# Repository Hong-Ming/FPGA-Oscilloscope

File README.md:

# FPGA Oscilloscope

## Table of Contents
- [Intorduction](#intorduction)
- [Directory Tree](#directory-tree)
- [Project Info](#project-info)
- [Framework and Layout](#framework-and-layout)
- [Contributor](#contributor)

## Intorduction
We built a simple oscilloscope using Nexys 4 DDR board and PCB. First, the PCB transforms the input voltage signal into a signal with an acceptable voltage range for the FPGA board input, as well as generating knobs' control signal. The FPGA board then takes the processed signal and control signal to display waveforms, change voltage scale, adjust sweep time, etc. This work is the final project of the Digital Laboratory class at NCTU. [ [Demo Video](https://www.youtube.com/watch?v=sgIzcKYEROs&feature=youtu.be&ab_channel=AlexLi) ]

## Directory Tree
<pre>
FPGA_Oscilloscope/
├─ Demo Video/ ..................... 
│  └─ Demo Video.mp4 ............... 
├─ FPGA_Code/ ...................... System Verilog code for oscilloscope
│  ├─ Oscilloscope.sv .............. Main Function
│  ├─ Control.sv ................... Function for processing control signal
│  ├─ Sampling.sv .................. Function for sampling signal
│  ├─ Data_transfer.sv ............. Choose sample data based on scale
│  ├─ Sampling_time.sv ............. Choose sample time based on scale
│  ├─ VGA.sv ....................... Function for displaying information on screen.
│  ├─ Trig_display.sv .............. Display trigger info
│  ├─ Time_display.sv .............. Display time info
│  ├─ Channel_display.sv ........... Display waveform
│  ├─ Info_display.sv .............. Subfunction for displaying info
│  ├─ Trig_info.sv ................. Subfunction for displaying info
│  ├─ Time_info.sv ................. Subfunction for displaying info
│  ├─ Scale_tag.sv ................. For output scale
│  ├─ Word.sv ...................... For bitmap-fonts
│  ├─ Word_move.sv ................. For bitmap-fonts
│  ├─ DFF.sv ....................... D Flip flop
│  ├─ clk_div_2.sv ................. Clock
│  ├─ Clk_div_4.sv ................. Clock
│  ├─ clk_div_16.sv ................ Clock
│  └─ clk_div_256.sv ............... Clock
└─ PCB/ ............................ Input rectifier circuit design
   ├─ MAX6818.lbr .................. ICL7660CAS Library File
   ├─ Oscilloscope.brd ............. PCB board file
   ├─ Oscilloscope.sch ............. PCB schematic file
   └─ Gerber/ ...................... Directory contains layout files
</pre>

## Project Info
- **HDL**: [SystemVerilog](https://en.wikipedia.org/wiki/SystemVerilog)
- **FPGA Board**: [Nexys 4 DDR](https://reference.digilentinc.com/reference/programmable-logic/nexys-4-ddr/start)
- **PCB Layout Software**: [EAGLE](https://www.autodesk.com/products/eagle/overview?plc=F360&term=1-YEAR&support=ADVANCED&quantity=1)

## Framework and Layout

**Framework**:

**Input Rectifier Circuit Schematic**:

**Input Rectifier Circuit Layout**:

## Contributor
- [Hong-Ming Chiu](https://hong-ming.github.io/)
- [Huan-Jung Lee]()

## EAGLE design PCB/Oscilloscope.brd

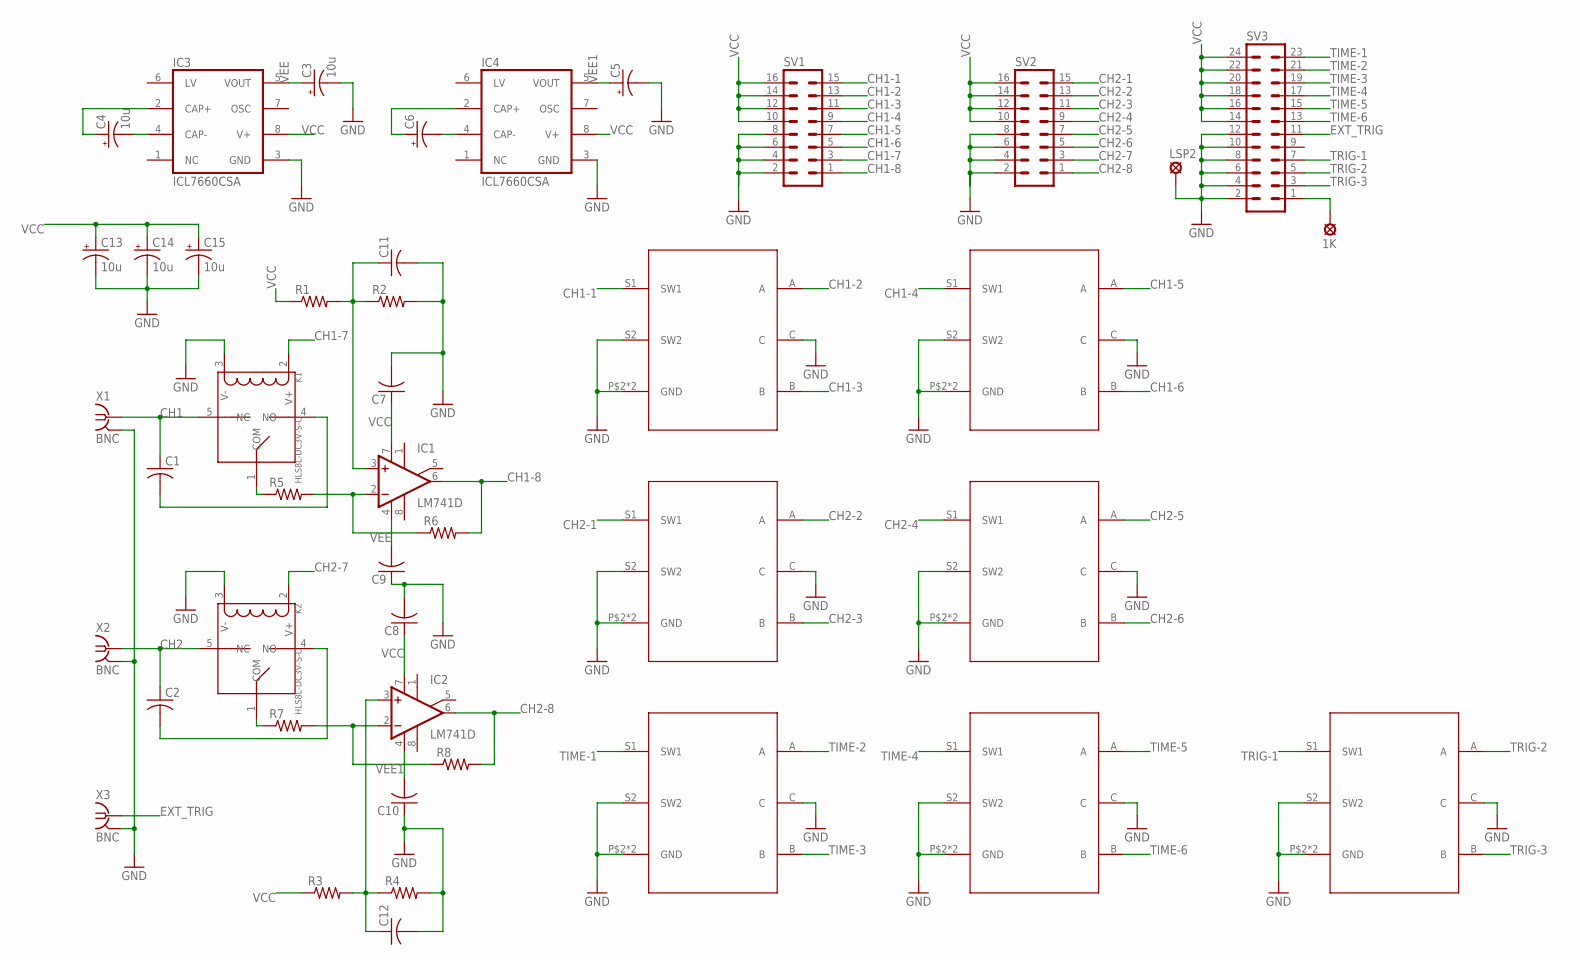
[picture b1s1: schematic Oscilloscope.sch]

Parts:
1K: LSP11
C1, C12: C-USC0402K; C0402K
C2, C7, C8, C9, C10, C11: C-USC0402; C0402
C3, C4, C13, C14, C15: 10u; E2-5
C5, C6: CPOL-USE2-5; E2-5
IC1, IC2: LM741D; SO08
IC3, IC4: ICL7660CSA; SO08
K1, K2: HLS8L-DC3V-S-C; REY5-19.0X15.0X15.0MM
LSP2: LSP11
R1, R2, R3, R4, R5, R6, R7, R8: R-US_R0402; R0402
SV1, SV2: MA08-2
SV3: MA12-2
U$2, U$3, U$4, U$5, U$6, U$7, U$8: EC11S
X1, X2, X3: BNC

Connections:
CH1: C1.1, K1.5 (NC), X1.P$1 (SIG)
CH1-1: SV1.15, U$3.S1 (SW1)
CH1-2: SV1.13, U$3.A
CH1-3: SV1.11, U$3.B
CH1-4: SV1.9, U$4.S1 (SW1)
CH1-5: SV1.7, U$4.A
CH1-6: SV1.5, U$4.B
CH1-7: K1.2 (V+), SV1.3
CH1-8: IC1.6 (OUT), R6.2, SV1.1
CH2: C2.1, K2.5 (NC), X2.P$1 (SIG)
CH2-1: SV2.15, U$2.S1 (SW1)
CH2-2: SV2.13, U$2.A
CH2-3: SV2.11, U$2.B
CH2-4: SV2.9, U$5.S1 (SW1)
CH2-5: SV2.7, U$5.A
CH2-6: SV2.5, U$5.B
CH2-7: K2.2 (V+), SV2.3
CH2-8: IC2.6 (OUT), R8.2, SV2.1
EXT_TRIG: SV3.11, X3.P$1 (SIG)
GND: C3.-, C5.-, C7.2, C8.2, C9.1, C10.1, C11.2, C12.2, C13.-, C14.-, C15.-, IC3.3 (GND), IC4.3 (GND), K1.3 (V-), K2.3 (V-), LSP2.MP, R2.2, R4.2, SV1.2, SV1.4, SV1.6, SV1.8, SV2.2, SV2.4, SV2.6, SV2.8, SV3.2, SV3.4, SV3.6, SV3.8, SV3.10, SV3.12, U$2.C, U$2.P$2 (GND), U$2.P$3 (GND), U$2.S2 (SW2), U$3.C, U$3.P$2 (GND), U$3.P$3 (GND), U$3.S2 (SW2), U$4.C, U$4.P$2 (GND), U$4.P$3 (GND), U$4.S2 (SW2), U$5.C, U$5.P$2 (GND), U$5.P$3 (GND), U$5.S2 (SW2), U$6.C, U$6.P$2 (GND), U$6.P$3 (GND), U$6.S2 (SW2), U$7.C, U$7.P$2 (GND), U$7.P$3 (GND), U$7.S2 (SW2), U$8.C, U$8.P$2 (GND), U$8.P$3 (GND), U$8.S2 (SW2), X1.P$2 (GND), X1.P$3 (GND), X1.P$4 (GND), X1.P$5 (GND), X2.P$2 (GND), X2.P$3 (GND), X2.P$4 (GND), X2.P$5 (GND), X3.P$2 (GND), X3.P$3 (GND), X3.P$4 (GND), X3.P$5 (GND)
unnamed: C1.2, K1.4 (NO)
unnamed: C2.2, K2.4 (NO)
unnamed: IC2.2 (-IN), R7.2, R8.1
unnamed: C4.-, IC3.4 (CAP-)
unnamed: C4.+, IC3.2 (CAP+)
unnamed: C6.-, IC4.4 (CAP-)
unnamed: C6.+, IC4.2 (CAP+)
unnamed: C11.1, IC1.3 (+IN), R1.2, R2.1
unnamed: C12.1, IC2.3 (+IN), R3.2, R4.1
unnamed: 1K.MP, SV3.1
unnamed: K1.1 (COM), R5.1
unnamed: IC1.2 (-IN), R5.2, R6.1
unnamed: K2.1 (COM), R7.1
TIME-1: SV3.23, U$6.S1 (SW1)
TIME-2: SV3.21, U$6.A
TIME-3: SV3.19, U$6.B
TIME-4: SV3.17, U$7.S1 (SW1)
TIME-5: SV3.15, U$7.A
TIME-6: SV3.13, U$7.B
TRIG-1: SV3.7, U$8.S1 (SW1)
TRIG-2: SV3.5, U$8.A
TRIG-3: SV3.3, U$8.B
VCC: C7.1, C8.1, C13.+, C14.+, C15.+, IC1.7 (V+), IC2.7 (V+), IC3.8 (V+), IC4.8 (V+), R1.1, R3.1, SV1.10, SV1.12, SV1.14, SV1.16, SV2.10, SV2.12, SV2.14, SV2.16, SV3.14, SV3.16, SV3.18, SV3.20, SV3.22, SV3.24
VEE: C3.+, C9.2, IC1.4 (V-), IC3.5 (VOUT)
VEE1: C5.+, C10.2, IC2.4 (V-), IC4.5 (VOUT)

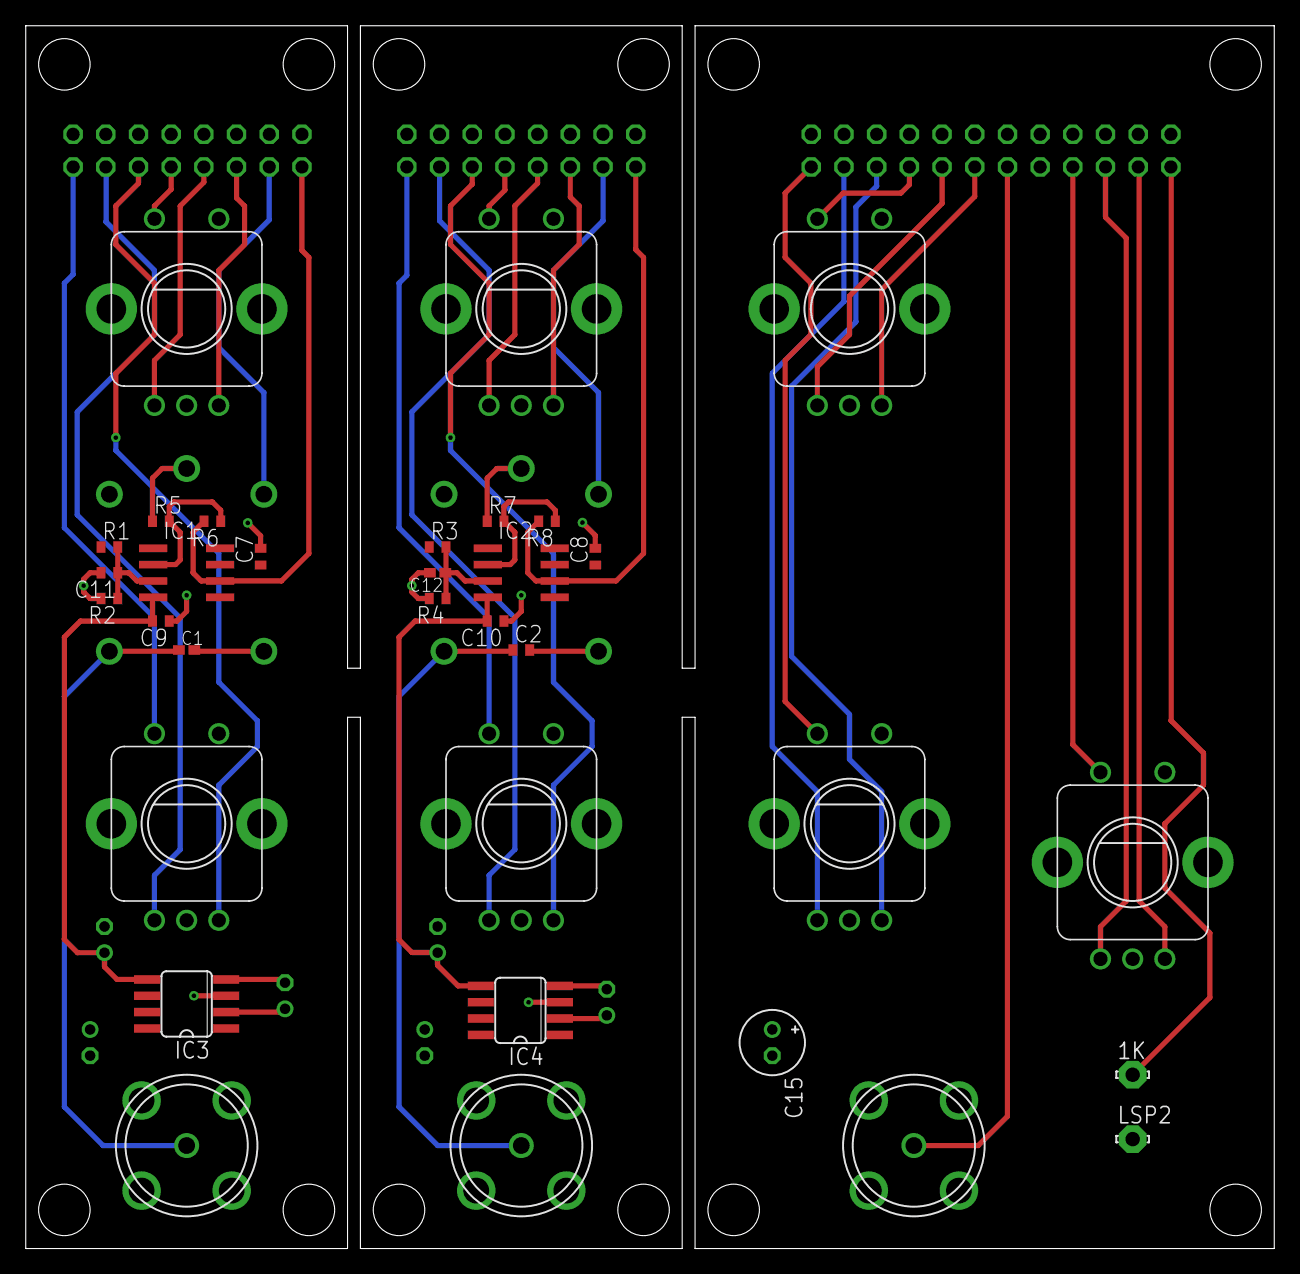
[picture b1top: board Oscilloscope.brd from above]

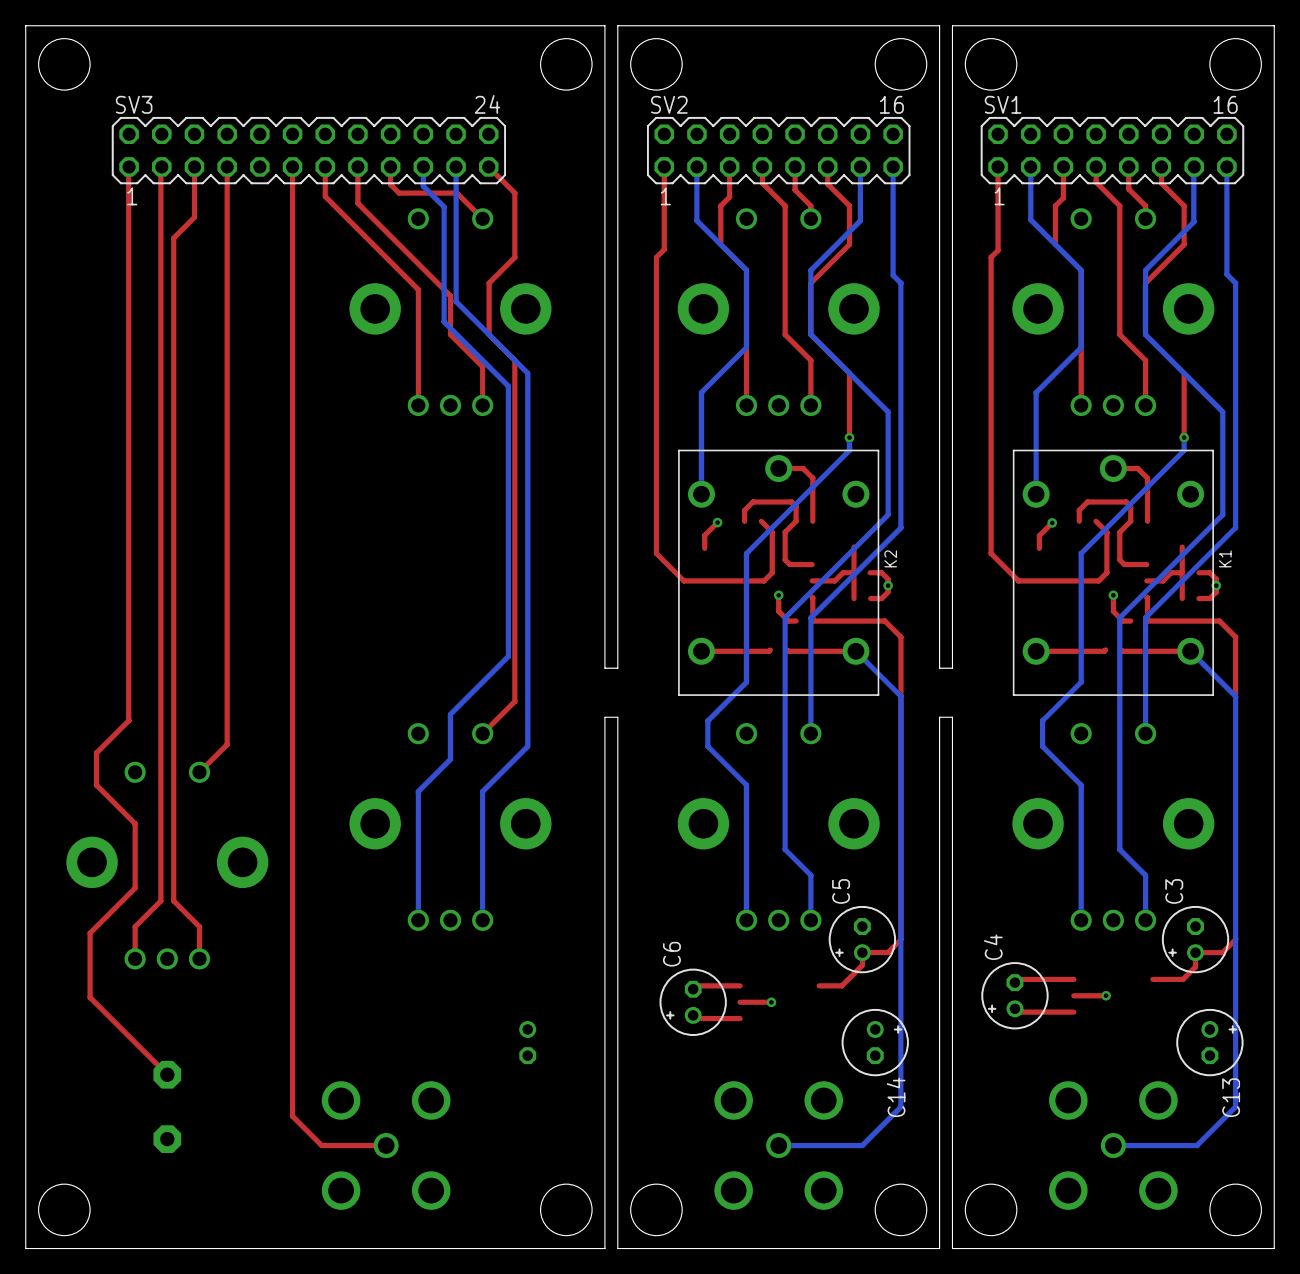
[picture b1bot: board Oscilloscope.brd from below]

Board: 2 copper layers, 97.0 x 95.0 mm, 44 parts (11 on the bottom side), 45 nets.

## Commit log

2020-11-17 upload html
2020-11-18 upload demo video
